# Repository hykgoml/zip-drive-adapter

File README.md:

# Zip Drive Adapter

This adapter lets you plug a **parallel-port Iomega Zip 100** into a modern computer over USB. A Raspberry Pi Pico 2 (RP2350) speaks the Zip's PPA protocol on the parallel side, and the computer sees a USB mass-storage device.

<p align="center"><br><a href="https://retrorecoveryrestore.com/">retrorecoveryrestore.com</a></p>

## Board (v0.6)
<p align="center">
  
  &nbsp;
  
</p>
<p align="center"><sub>KiCad 3D renders of the bare board in the ordered colours (black solder mask, yellow silkscreen). Top on the left, bottom on the right.</sub></p>

<p align="center"><sub>Assembled preview from PCBPA's 3D view (its default green and white colours), showing the Pico 2 on its headers, the status LEDs and the DB25.</sub></p>

## Status
- **Board v0.6**: ordered from PCBWay on 2026-11-25, due 2026-12-01. Not yet built or tested. KiCad DRC is clean, and so are PCBPA's checks under PCBWay's standard rules.
- **Firmware**: not started. The plan is in [CLAUDE.md](CLAUDE.md).

## ⚠️ Parallel-port devices only
DB25 is just the connector shape, and several incompatible interfaces use it. This board is a **parallel-port (IEEE 1284) host**: 8 bidirectional data lines, 4 control outputs and 5 status inputs, with ground on pins 18–25.

| DB25 device | OK to connect? |
|---|---|
| **Parallel-port devices**: Zip 100 parallel, printers, parallel scanners and drives | ✅ The hardware is compatible. Each device needs its own firmware; the Zip 100 (PPA protocol) is the target. Zip Plus and Zip 250 parallel use a different protocol (IMM). |
| **RS-232 serial on DB25**: modems, terminals | ❌ **Can damage the board.** Serial uses about ±12V, and the 74LVC245 buffers only tolerate roughly −0.5V to 6.5V. |
| **SCSI on DB25**: Mac-style SCSI, *including the SCSI Zip 100* | ❌ **Don't plug it in.** The pinout is completely different, and SCSI puts +5V termination power on pin 25, which this board ties to ground. |

**Check your Zip before you connect it.** The SCSI Zip 100 uses the same DB25 connector as the parallel one. The SCSI model has two DB25 ports plus SCSI ID and termination switches on the back. The parallel model has a single DB25 and is labelled as a parallel-port drive.

## Ordering from PCBWay (v0.6)
**Step-by-step guide: [ORDERING.md](ORDERING.md)**, covering every field on PCBWay's quote form, the Gerber upload and the review.

Upload `zipbridge_v0.6_gerbers.zip`, or take it from the [v0.6 release](../../releases/tag/v0.6).

| Option | Value |
|---|---|
| Layers | 2 |
| Size | 66 × 79.8 mm |
| Thickness | 1.6 mm |
| Min track / spacing | 0.25 / 0.2 mm (6/6 mil or better is fine) |
| Min hole | 0.3 mm |
| Surface finish | HASL |
| **Solder mask** | **Black** |
| **Silkscreen** | **Yellow** |

Both are standard PCBWay options. The bottom-side artwork is drawn for light ink on a dark mask. The Ick logo prints in yellow on black, like the sticker. The QR code prints its light background in yellow, and the black board shows through as the modules (normal QR polarity). With a light mask and dark silkscreen, both would come out inverted.

## Bill of Materials
Every part is through-hole. The same list is in [BOM.md](BOM.md), with more notes and a [where-to-buy table](BOM.md#where-to-buy), and as a spreadsheet in [BOM.csv](BOM.csv).

| Qty | Refs | Part | Value / spec | Notes |
|---:|---|---|---|---|
| 1 | U4 | Raspberry Pi Pico 2 (RP2350) | — | Component side up, USB at the left edge · [Amazon](https://www.amazon.com/dp/B0DG3QPQCT) |
| 3 | U1–U3 | SN74LVC245AN | DIP-20 transceiver | U1 data, U2 control, U3 status. Must be **LVC** (3.3V, 5V-tolerant inputs) · buy from [DigiKey](https://www.digikey.com/en/products/result?keywords=SN74LVC245AN) or [Mouser](https://www.mouser.com/c/?q=SN74LVC245AN), not Amazon |
| 1 | J1 | DB25 female, right-angle, PCB mount | 0.318" setback, board locks | [Amazon B00C58IPSO](https://www.amazon.com/dp/B00C58IPSO) (bought) · alt. [McMaster 5063N19](https://www.mcmaster.com/5063N19) |
| 8 | R1–R8 | Resistor | 100Ω ¼W | Data-line series · [resistor kit](https://www.amazon.com/dp/B07P3MFG5D) (covers all resistors) |
| 7 | R9–R15 | Resistor | 10kΩ ¼W | Status and OE# pull-ups |
| 4 | R16–R19 | Resistor | 470Ω ¼W, **standing**, 2.54mm | LED series |
| 3 | C1–C3 | Ceramic capacitor | 100nF 50V, 2.5mm | Decoupling · [Amazon](https://www.amazon.com/dp/B0DFQ93CPT) |
| 1 | D1 | LED 3mm | Green | **PWR** (3.3V) · [LED kit](https://www.amazon.com/dp/B07CB44M2Z) (covers D1–D4) |
| 1 | D2 | LED 3mm | Yellow | **READY** (GP22) |
| 1 | D3 | LED 3mm | Green | **READ**, Zip→PC (GP20) |
| 1 | D4 | LED 3mm | Red | **WRITE**, PC→Zip (GP21) |
| 3 | — | DIP-20 IC socket, 0.3" | — | For U1–U3 · [Amazon](https://www.amazon.com/dp/B07H3RPFH8) |
| 2 | — | 1×20 female header, 2.54mm | — | Optional: removable Pico · [Amazon](https://www.amazon.com/dp/B0CFDV41T9) |
| 3 | — | M3 standoff + screw | — | Optional: mounting holes H1–H3 · [Amazon](https://www.amazon.com/dp/B0F297R23T) |
| 1 | — | PCB | v0.6, black mask / yellow silk | See [ORDERING.md](ORDERING.md) |

You also need the Zip's original DB25 male–male cable, a micro-USB cable, and the Zip's own power supply. Use red, green or yellow LEDs; blue and white are too dim at 3.3V. The GPIO map is in [CLAUDE.md](CLAUDE.md#gpio-map).

**Status LEDs** are on the right edge. PWR is lit whenever the board has 3.3V. READY, READ and WRITE are driven by the firmware.

**Footprints:** the Pico 2 and DB25 footprints match KiCad's reference footprints exactly. From v0.4 on, the board edge is placed so the 0.318" DB25's flange sits flush.

## Files
| File | What it is |
|---|---|
| `zipbridge_vX.Y.kicad_pcb` | Board (KiCad) |
| `zipbridge_vX.Y.pcbpa` | The same board in PCBPA |
| `zipbridge_vX.Y_gerbers.zip` | Fab files |
| `build.py`, `router.py`, `pour.py` | Board generator: place → route → pour |
| `BOM.md`, `BOM.csv` | Bill of materials |
| `ORDERING.md` | How to order the PCB from PCBWay |
| `models/` | 3D model (STL) of the DB25, used by the `.pcbpa` board's 3D view. Made from KiCad's model by `art/wrl_to_stl.py` |
| `firmware/` | Bring-up firmware for the Pico 2: USB serial console to test every LED, buffer and DB25 signal without a Zip drive. Checklist in `firmware/BRINGUP.md` |
| `images/` | Board renders |
| `art/` | Logo and QR source images, plus `add_artwork.py`, which puts them on the bottom silkscreen |

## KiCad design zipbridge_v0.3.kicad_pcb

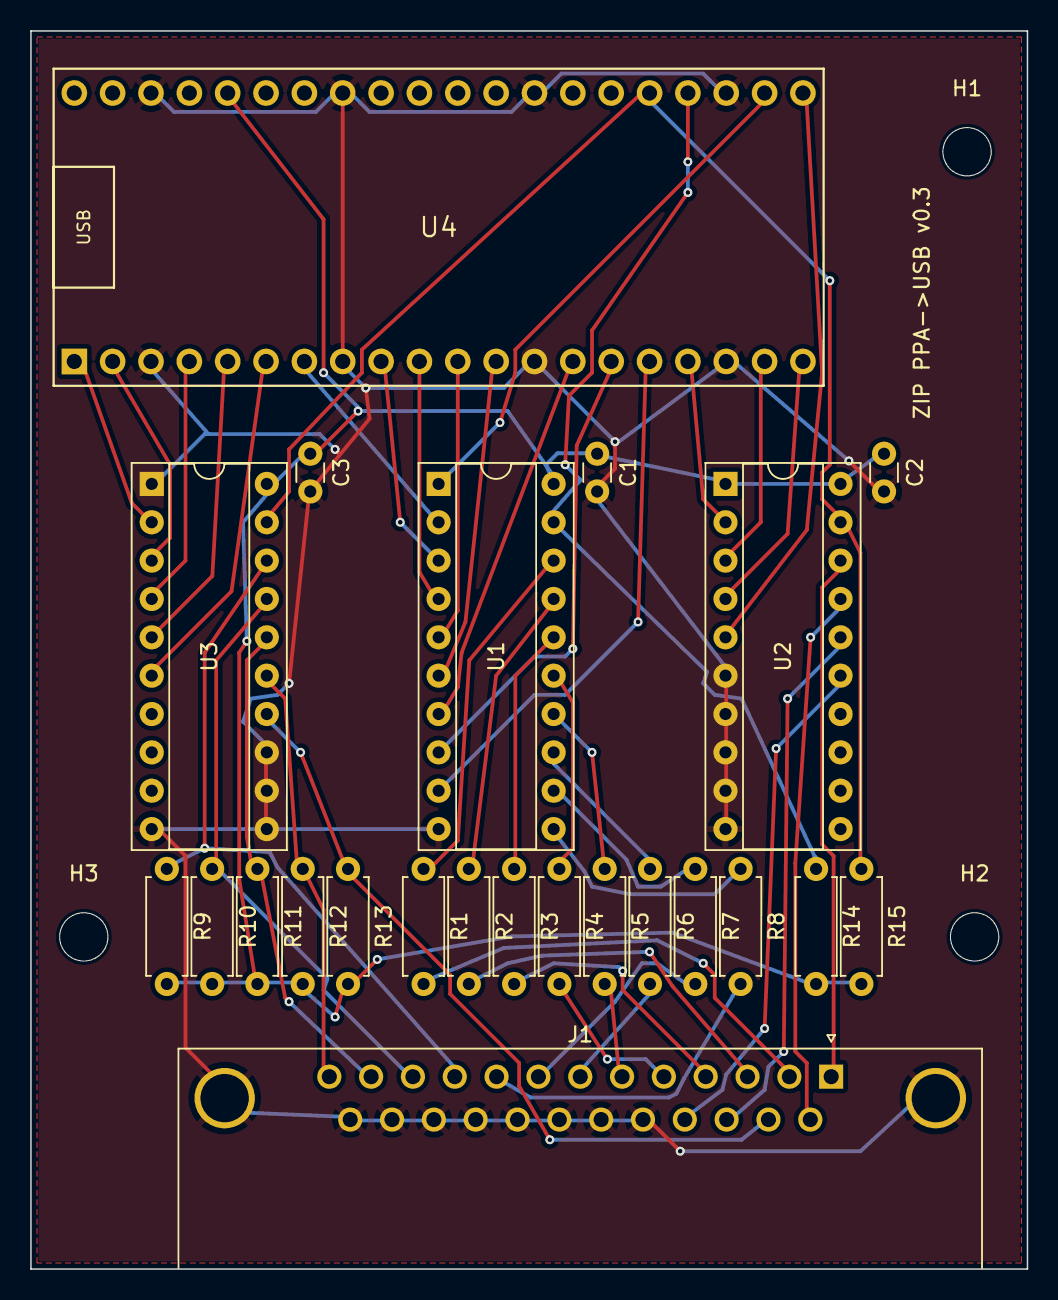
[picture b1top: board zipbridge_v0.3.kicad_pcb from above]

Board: 2 copper layers, 66.0 x 82.0 mm, 26 parts (0 on the bottom side), 47 nets.

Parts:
C1, C2, C3: 100n; C_Disc_D3.0mm_W1.6mm_P2.50mm
H1, H2, H3: M3; MountingHole_3.2mm_M3
J1: DB25 Female (to Zip); DSUB-25_Female_Horizontal_P2.77x2.84mm_EdgePinOffset9.90mm_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
R1, R2, R3, R4, R5, R6, R7, R8: 100; R_Axial_DIN0207_L6.3mm_D2.5mm_P7.62mm_Horizontal
R9, R10, R11, R12, R13, R14, R15: 10k; R_Axial_DIN0207_L6.3mm_D2.5mm_P7.62mm_Horizontal
U1: 74LVC245 DATA; DIP-20_W7.62mm_Socket
U2: 74LVC245 CTRL; DIP-20_W7.62mm_Socket
U3: 74LVC245 STATUS; DIP-20_W7.62mm_Socket
U4: Pico 2 (RP2350)

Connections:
+3V3: C1.1, C2.1, C3.1, R9.2, R10.2, R11.2, R12.2, R13.2, R14.2, R15.2, U1.20, U2.1, U2.20, U3.20, U4.36
BUF_D0: R1.1, U1.18
BUF_D1: R2.1, U1.17
BUF_D2: R3.1, U1.16
BUF_D3: R4.1, U1.15
BUF_D4: R5.1, U1.14
BUF_D5: R6.1, U1.13
BUF_D6: R7.1, U1.12
BUF_D7: R8.1, U1.11
CTL_OE#: R15.1, U2.19, U3.19, U4.25
DATA_DIR: U1.1, U4.22
DATA_OE#: R14.1, U1.19, U4.24
GND: C1.2, C2.2, C3.2, J1.0, J1.18, J1.19, J1.20, J1.21, J1.22, J1.23, J1.24, J1.25, U1.10, U2.6, U2.7, U2.8, U2.9, U2.10, U3.1, U3.10, U3.11, U3.12, U3.13, U4.3, U4.8, U4.13, U4.18, U4.23, U4.28, U4.33, U4.38
GP0: U3.2, U4.1
GP1: U3.3, U4.2
GP2: U3.4, U4.4
GP3: U3.5, U4.5
GP4: U3.6, U4.6
GP5: U1.2, U4.7
GP6: U1.3, U4.9
GP7: U1.4, U4.10
GP8: U1.5, U4.11
GP9: U1.6, U4.12
GP10: U1.7, U4.14
GP11: U1.8, U4.15
GP12: U1.9, U4.16
GP13: U2.2, U4.17
GP14: U2.3, U4.19
GP15: U2.4, U4.20
GP16: U2.5, U4.21
LPT_ACK: J1.10, R9.1, U3.18
LPT_AUTOFD#: J1.14, U2.17
LPT_BUSY: J1.11, R10.1, U3.17
LPT_D0: J1.2, R1.2
LPT_D1: J1.3, R2.2
LPT_D2: J1.4, R3.2
LPT_D3: J1.5, R4.2
LPT_D4: J1.6, R5.2
LPT_D5: J1.7, R6.2
LPT_D6: J1.8, R7.2
LPT_D7: J1.9, R8.2
LPT_ERR: J1.15, R13.1, U3.14
LPT_INIT#: J1.16, U2.16
LPT_PE: J1.12, R11.1, U3.16
LPT_SEL: J1.13, R12.1, U3.15
LPT_SELIN#: J1.17, U2.15
LPT_STROBE#: J1.1, U2.18
